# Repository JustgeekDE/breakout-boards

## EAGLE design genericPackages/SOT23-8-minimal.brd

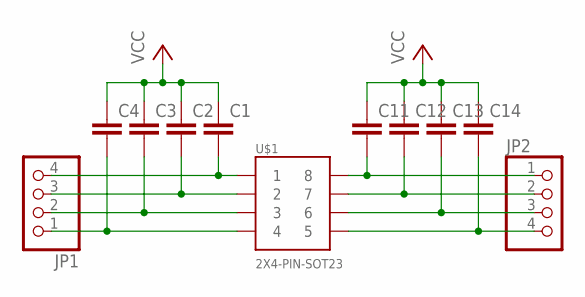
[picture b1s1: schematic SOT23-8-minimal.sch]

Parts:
C1, C2, C3, C4, C11, C12, C13, C14: C-EUC0603; C0603
JP1, JP2: PINHD-1X4; 1X04
U$1: 2X4-PIN-SOT23; SOT23-8

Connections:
1: C1.2, JP1.4, U$1.P$1 (1)
2: C2.2, JP1.3, U$1.P$2 (2)
3: C3.2, JP1.2, U$1.P$3 (3)
4: C4.2, JP1.1, U$1.P$4 (4)
5: C14.2, JP2.4, U$1.P$5 (5)
6: C13.2, JP2.3, U$1.P$6 (6)
7: C12.2, JP2.2, U$1.P$7 (7)
8: C11.2, JP2.1, U$1.P$8 (8)
VCC: C1.1, C2.1, C3.1, C4.1, C11.1, C12.1, C13.1, C14.1

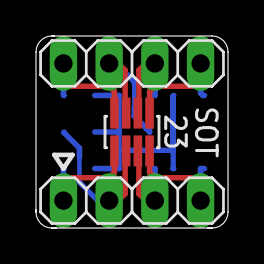
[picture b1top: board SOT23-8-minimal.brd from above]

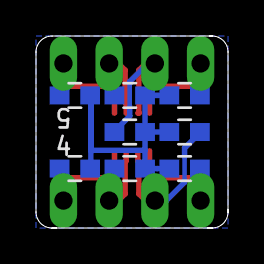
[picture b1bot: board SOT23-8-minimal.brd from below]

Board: 2 copper layers, 10.7 x 10.7 mm, 11 parts (8 on the bottom side), 9 nets.

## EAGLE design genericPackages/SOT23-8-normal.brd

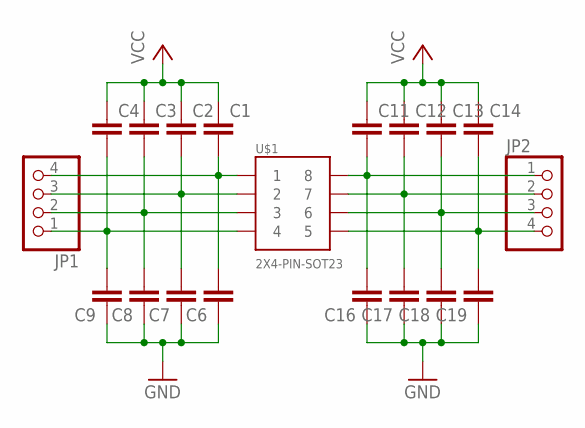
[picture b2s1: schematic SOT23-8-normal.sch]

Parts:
C1, C2, C3, C4, C11, C12, C13, C14: C-EUC0603; C0603
C6, C7, C8, C9, C16, C17, C18, C19: C-EUC0805; C0805
JP1, JP2: PINHD-1X4; 1X04
U$1: 2X4-PIN-SOT23; SOT23-8

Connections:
1: C1.2, C6.2, JP1.4, U$1.P$1 (1)
2: C2.2, C7.2, JP1.3, U$1.P$2 (2)
3: C3.2, C8.2, JP1.2, U$1.P$3 (3)
4: C4.2, C9.2, JP1.1, U$1.P$4 (4)
5: C14.2, C19.2, JP2.4, U$1.P$5 (5)
6: C13.2, C18.2, JP2.3, U$1.P$6 (6)
7: C12.2, C17.2, JP2.2, U$1.P$7 (7)
8: C11.2, C16.2, JP2.1, U$1.P$8 (8)
GND: C6.1, C7.1, C8.1, C9.1, C16.1, C17.1, C18.1, C19.1
VCC: C1.1, C2.1, C3.1, C4.1, C11.1, C12.1, C13.1, C14.1

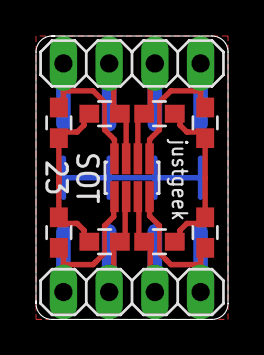
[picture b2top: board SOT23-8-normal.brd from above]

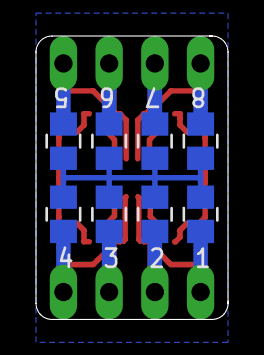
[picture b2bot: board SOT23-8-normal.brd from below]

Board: 2 copper layers, 10.7 x 15.7 mm, 19 parts (8 on the bottom side), 10 nets.

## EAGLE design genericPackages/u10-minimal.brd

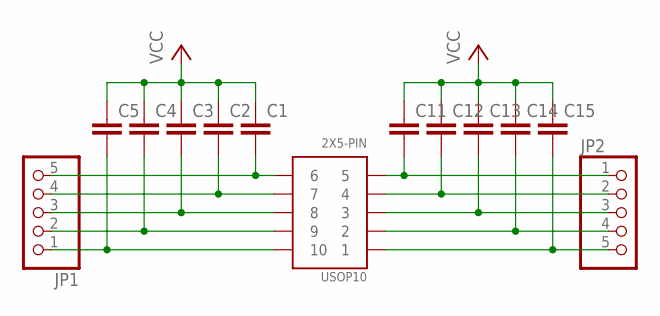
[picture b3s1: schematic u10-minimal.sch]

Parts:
C1, C2, C3, C4, C5, C11, C12, C13, C14, C15: C-EUC0603; C0603
JP1, JP2: PINHD-1X5; 1X05
USOP10: 2X5-PIN; USOP10

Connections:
1: C15.2, JP2.5, USOP10.P$1 (1)
2: C14.2, JP2.4, USOP10.P$2 (2)
3: C13.2, JP2.3, USOP10.P$3 (3)
4: C12.2, JP2.2, USOP10.P$4 (4)
5: C11.2, JP2.1, USOP10.P$5 (5)
6: C1.2, JP1.5, USOP10.P$6 (6)
7: C2.2, JP1.4, USOP10.P$7 (7)
8: C3.2, JP1.3, USOP10.P$8 (8)
9: C4.2, JP1.2, USOP10.P$9 (9)
10: C5.2, JP1.1, USOP10.P$10 (10)
VCC: C1.1, C2.1, C3.1, C4.1, C5.1, C11.1, C12.1, C13.1, C14.1, C15.1

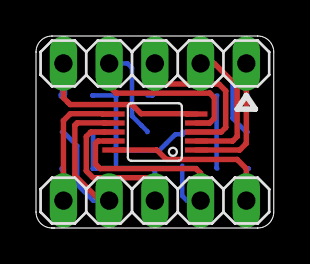
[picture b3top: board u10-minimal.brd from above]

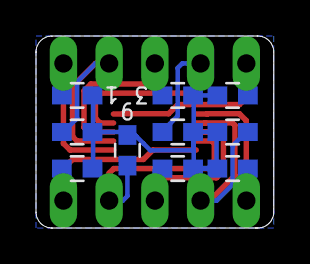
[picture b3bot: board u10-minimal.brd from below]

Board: 2 copper layers, 13.2 x 10.7 mm, 13 parts (10 on the bottom side), 11 nets.

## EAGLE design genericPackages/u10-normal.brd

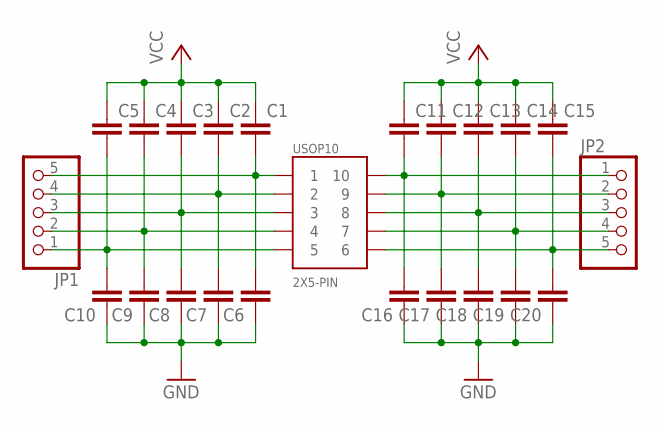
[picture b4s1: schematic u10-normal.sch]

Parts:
C1, C2, C3, C4, C5, C11, C12, C13, C14, C15: C-EUC0603; C0603
C6, C7, C8, C9, C10, C16, C17, C18, C19, C20: C-EUC0805; C0805
JP1, JP2: PINHD-1X5; 1X05
USOP10: 2X5-PIN; USOP10

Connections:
1: C1.2, C6.2, JP1.5, USOP10.P$1 (1)
2: C2.2, C7.2, JP1.4, USOP10.P$2 (2)
3: C3.2, C8.2, JP1.3, USOP10.P$3 (3)
4: C4.2, C9.2, JP1.2, USOP10.P$4 (4)
5: C5.2, C10.2, JP1.1, USOP10.P$5 (5)
GND: C6.1, C7.1, C8.1, C9.1, C10.1, C16.1, C17.1, C18.1, C19.1, C20.1
unnamed: C15.2, C20.2, JP2.5, USOP10.P$6 (6)
unnamed: C14.2, C19.2, JP2.4, USOP10.P$7 (7)
unnamed: C13.2, C18.2, JP2.3, USOP10.P$8 (8)
unnamed: C12.2, C17.2, JP2.2, USOP10.P$9 (9)
unnamed: C11.2, C16.2, JP2.1, USOP10.P$10 (10)
VCC: C1.1, C2.1, C3.1, C4.1, C5.1, C11.1, C12.1, C13.1, C14.1, C15.1

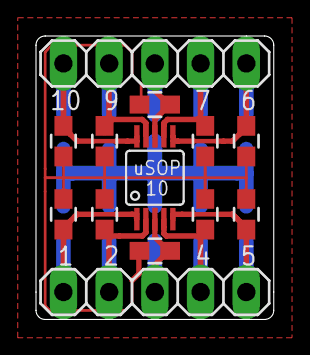
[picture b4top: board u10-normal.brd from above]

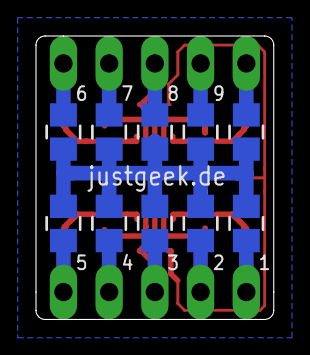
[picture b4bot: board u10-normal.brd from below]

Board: 2 copper layers, 13.2 x 15.7 mm, 23 parts (10 on the bottom side), 12 nets.

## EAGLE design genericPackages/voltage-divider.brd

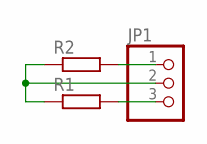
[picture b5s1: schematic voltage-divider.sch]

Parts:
JP1: PINHD-1X3; 1X03
R1, R2: R-EU_R0805; R0805

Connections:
unnamed: JP1.1, R2.2
unnamed: JP1.3, R1.2
unnamed: JP1.2, R1.1, R2.1

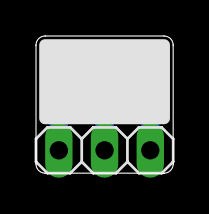
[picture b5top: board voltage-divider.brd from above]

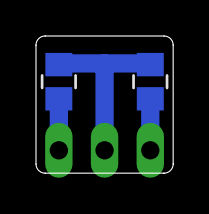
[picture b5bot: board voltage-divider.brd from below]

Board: 2 copper layers, 7.6 x 7.6 mm, 3 parts (2 on the bottom side), 3 nets.

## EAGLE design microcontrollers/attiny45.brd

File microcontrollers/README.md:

# Attiny 25/45/85
A minimal breakout board for AttinyX5 microcontrollers. The board is the size of a standard 8-pin DIP, but contains the reset pull-up and 100n decoupling capacitor.

On the top there is also a footprint, to use [Madworms Tiny AVR pogo pin programming adaptor](https://www.tindie.com/products/madworm/tiny-avr-isp-pogo-pin-programmig-adapter/).

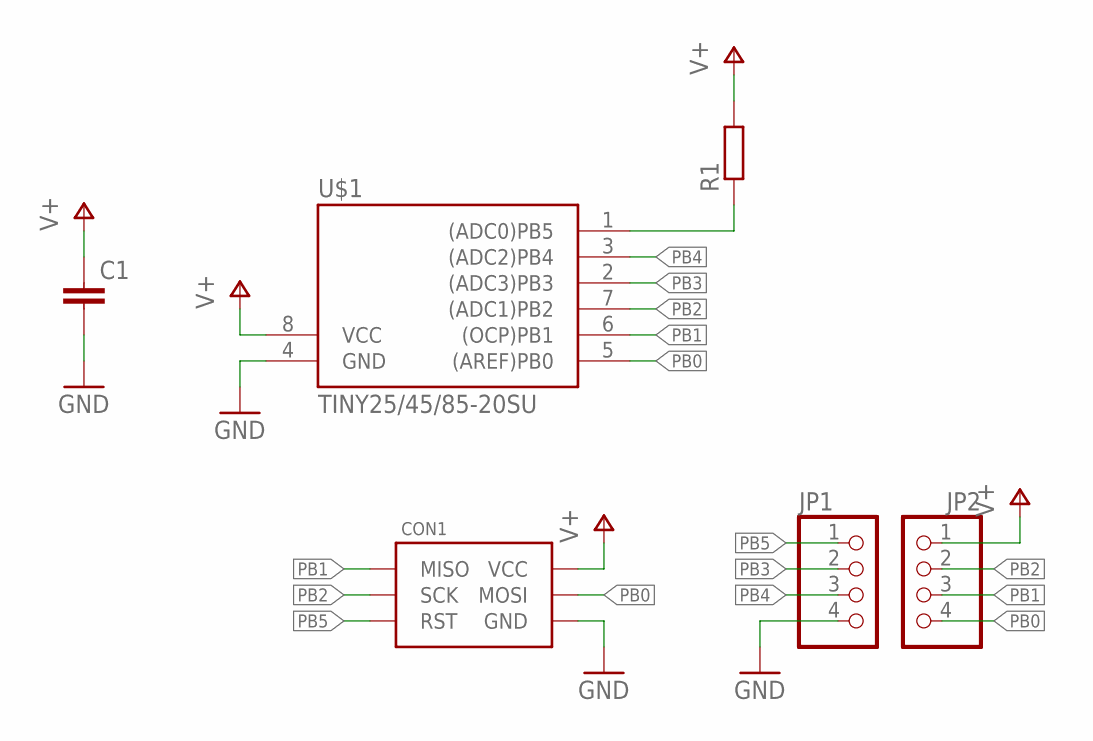
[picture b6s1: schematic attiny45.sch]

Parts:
C1: C-EUC0603; C0603
CON1: ISP-6_PIN-POGO; POGO-1.27-6_PIN-MADWORM
JP1, JP2: PINHD-1X4; 1X04
R1: R-EU_R0603; R0603
U$1: TINY25/45/85-20SU; SOIC8

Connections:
GND: C1.2, CON1.P$6 (GND), JP1.4, U$1.4 (GND)
PB0: CON1.P$4 (MOSI), JP2.4, U$1.5 ((AREF)PB0)
PB1: CON1.P$1 (MISO), JP2.3, U$1.6 ((OCP)PB1)
PB2: CON1.P$3 (SCK), JP2.2, U$1.7 ((ADC1)PB2)
PB3: JP1.2, U$1.2 ((ADC3)PB3)
PB4: JP1.3, U$1.3 ((ADC2)PB4)
PB5: CON1.P$5 (RST), JP1.1, R1.1, U$1.1 ((ADC0)PB5)
V+: C1.1, CON1.P$2 (VCC), JP2.1, R1.2, U$1.8 (VCC)

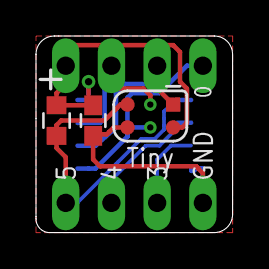
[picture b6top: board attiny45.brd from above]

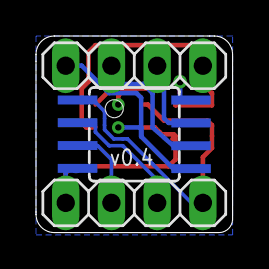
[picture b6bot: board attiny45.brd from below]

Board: 2 copper layers, 10.9 x 10.9 mm, 6 parts (3 on the bottom side), 8 nets.

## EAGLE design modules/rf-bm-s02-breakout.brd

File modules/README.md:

# RF BM S02
A breakout board for the cheap bluetooth module

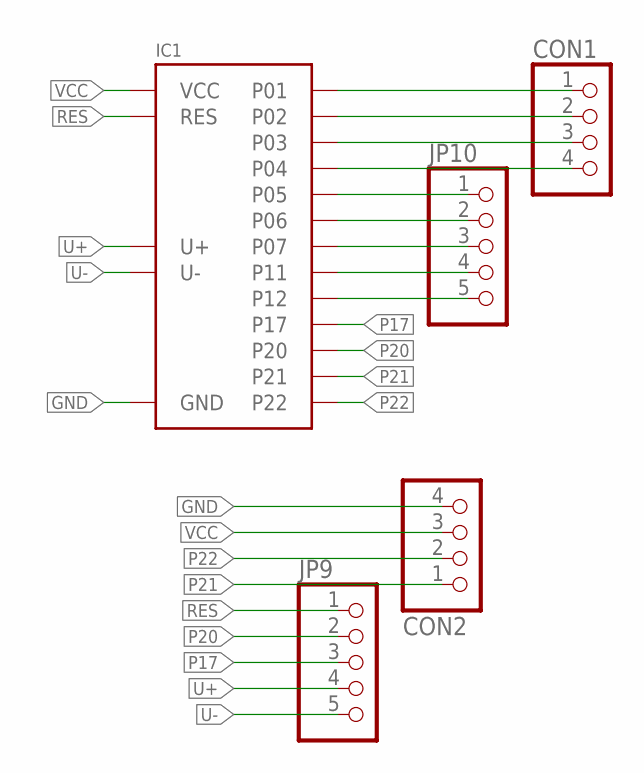
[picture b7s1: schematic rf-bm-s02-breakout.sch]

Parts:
CON1, CON2: GENERIC-1X4STRAIGHT; PINHEADER-100MIL-1X4-NOSILK
IC1: BLUETOOTH-RF-BM-S02; BLUETOOTH-RF-BM-S02-SMD
JP9, JP10: PINHD-1X5; 1X05

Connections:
GND: CON2.4, IC1.P$18 (GND)
P01: CON1.1, IC1.P$9 (P01)
P02: CON1.2, IC1.P$8 (P02)
P03: CON1.3, IC1.P$7 (P03)
P04: CON1.4, IC1.P$6 (P04)
P05: IC1.P$5 (P05), JP10.1
P06: IC1.P$4 (P06), JP10.2
P07: IC1.P$3 (P07), JP10.3
P11: IC1.P$2 (P11), JP10.4
P12: IC1.P$1 (P12), JP10.5
P17: IC1.P$12 (P17), JP9.3
P20: IC1.P$13 (P20), JP9.2
P21: CON2.1, IC1.P$15 (P21)
P22: CON2.2, IC1.P$16 (P22)
RES: IC1.P$14 (RES), JP9.1
U+: IC1.P$11 (U+), JP9.4
U-: IC1.P$10 (U-), JP9.5
VCC: CON2.3, IC1.P$17 (VCC)

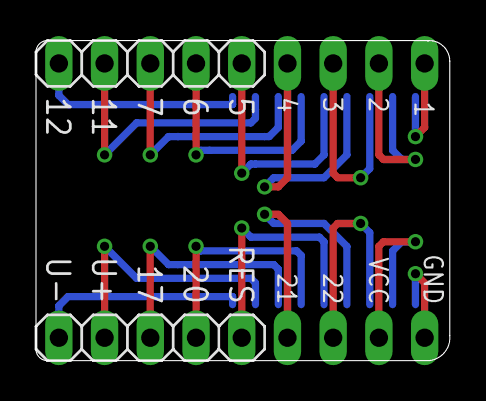
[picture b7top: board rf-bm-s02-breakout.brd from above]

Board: 2 copper layers, 23.0 x 17.8 mm, 5 parts (1 on the bottom side), 18 nets.
